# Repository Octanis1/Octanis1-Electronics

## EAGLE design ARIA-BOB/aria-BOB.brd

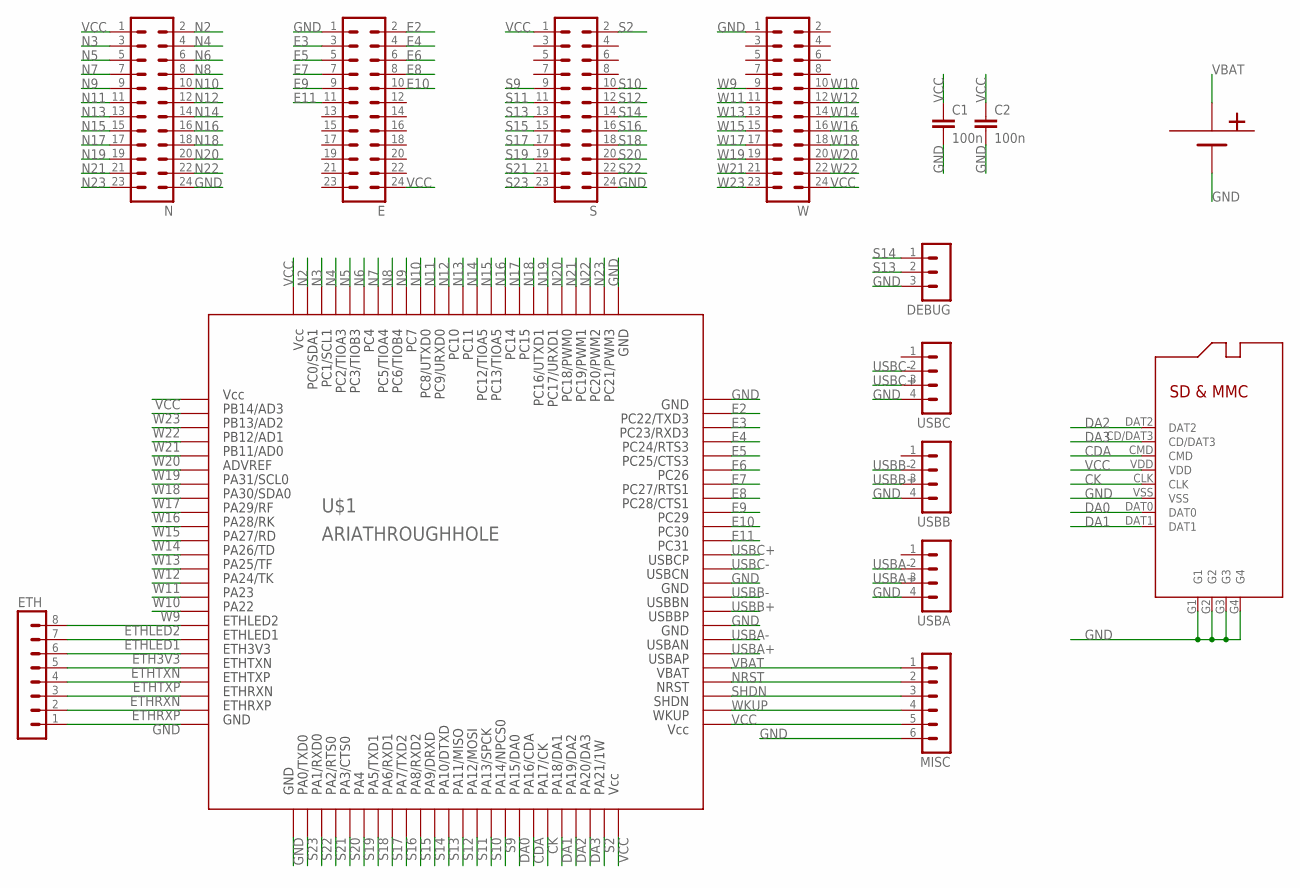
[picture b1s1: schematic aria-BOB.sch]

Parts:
C1, C2: 100n; C0603
DEBUG: MA03-1
E: MA12-2
ETH: MA08-1
MISC: MA06-1
N: MA12-2
S: MA12-2
U$1: ARIATHROUGHHOLE; ARIA-TROUGHHOLE
U$3: BAT; BAT-CR1220
U$4: MICRO-SD; MISCRO-SD
USBA: MA04-1
USBB: MA04-1
USBC: MA04-1
W: MA12-2

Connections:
CDA: U$1.S7, U$4.CMD
CK: U$1.S6, U$4.CLK
DA0: U$1.S8, U$4.DAT0
DA1: U$1.S5, U$4.DAT1
DA2: U$1.S4, U$4.DAT2
DA3: U$1.S3, U$4.CD/DAT3
E2: E.2, U$1.E2
E3: E.3, U$1.E3
E4: E.4, U$1.E4
E5: E.5, U$1.E5
E6: E.6, U$1.E6
E7: E.7, U$1.E7
E8: E.8, U$1.E8
E9: E.9, U$1.E9
E10: E.10, U$1.E10
E11: E.11, U$1.E11
ETH3V3: ETH.6, U$1.W6
ETHLED1: ETH.7, U$1.W7
ETHLED2: ETH.8, U$1.W8
ETHRXN: ETH.3, U$1.W3
ETHRXP: ETH.2, U$1.W2
ETHTXN: ETH.5, U$1.W5
ETHTXP: ETH.4, U$1.W4
GND: C1.2, C2.2, DEBUG.3, E.1, ETH.1, MISC.6, N.24, S.24, U$1.E1, U$1.E14, U$1.E17, U$1.N24, U$1.S24, U$1.W1, U$3.BAT-, U$4.G1, U$4.G2, U$4.G3, U$4.G4, U$4.VSS, USBA.4, USBB.4, USBC.4, W.1
N2: N.2, U$1.N2
N3: N.3, U$1.N3
N4: N.4, U$1.N4
N5: N.5, U$1.N5
N6: N.6, U$1.N6
N7: N.7, U$1.N7
N8: N.8, U$1.N8
N9: N.9, U$1.N9
N10: N.10, U$1.N10
N11: N.11, U$1.N11
N12: N.12, U$1.N12
N13: N.13, U$1.N13
N14: N.14, U$1.N14
N15: N.15, U$1.N15
N16: N.16, U$1.N16
N17: N.17, U$1.N17
N18: N.18, U$1.N18
N19: N.19, U$1.N19
N20: N.20, U$1.N20
N21: N.21, U$1.N21
N22: N.22, U$1.N22
N23: N.23, U$1.N23
NRST: MISC.2, U$1.E21
S2: S.2, U$1.S2
S9: S.9, U$1.S9
S10: S.10, U$1.S10
S11: S.11, U$1.S11
S12: S.12, U$1.S12
S13: DEBUG.2, S.13, U$1.S13
S14: DEBUG.1, S.14, U$1.S14
S15: S.15, U$1.S15
S16: S.16, U$1.S16
S17: S.17, U$1.S17
S18: S.18, U$1.S18
S19: S.19, U$1.S19
S20: S.20, U$1.S20
S21: S.21, U$1.S21
S22: S.22, U$1.S22
S23: S.23, U$1.S23
SHDN: MISC.3, U$1.E22
USBA+: U$1.E19, USBA.3
USBA-: U$1.E18, USBA.2
USBB+: U$1.E16, USBB.3
USBB-: U$1.E15, USBB.2
USBC+: U$1.E12, USBC.3
USBC-: U$1.E13, USBC.2
VBAT: MISC.1, U$1.E20, U$3.BAT1+ (BAT+), U$3.BAT+
VCC: C1.1, C2.1, E.24, MISC.5, N.1, S.1, U$1.E24, U$1.N1, U$1.S1, U$1.W24, U$4.VDD, W.24
W9: U$1.W9, W.9
W10: U$1.W10, W.10
W11: U$1.W11, W.11
W12: U$1.W12, W.12
W13: U$1.W13, W.13
W14: U$1.W14, W.14
W15: U$1.W15, W.15
W16: U$1.W16, W.16
W17: U$1.W17, W.17
W18: U$1.W18, W.18
W19: U$1.W19, W.19
W20: U$1.W20, W.20
W21: U$1.W21, W.21
W22: U$1.W22, W.22
W23: U$1.W23, W.23
WKUP: MISC.4, U$1.E23

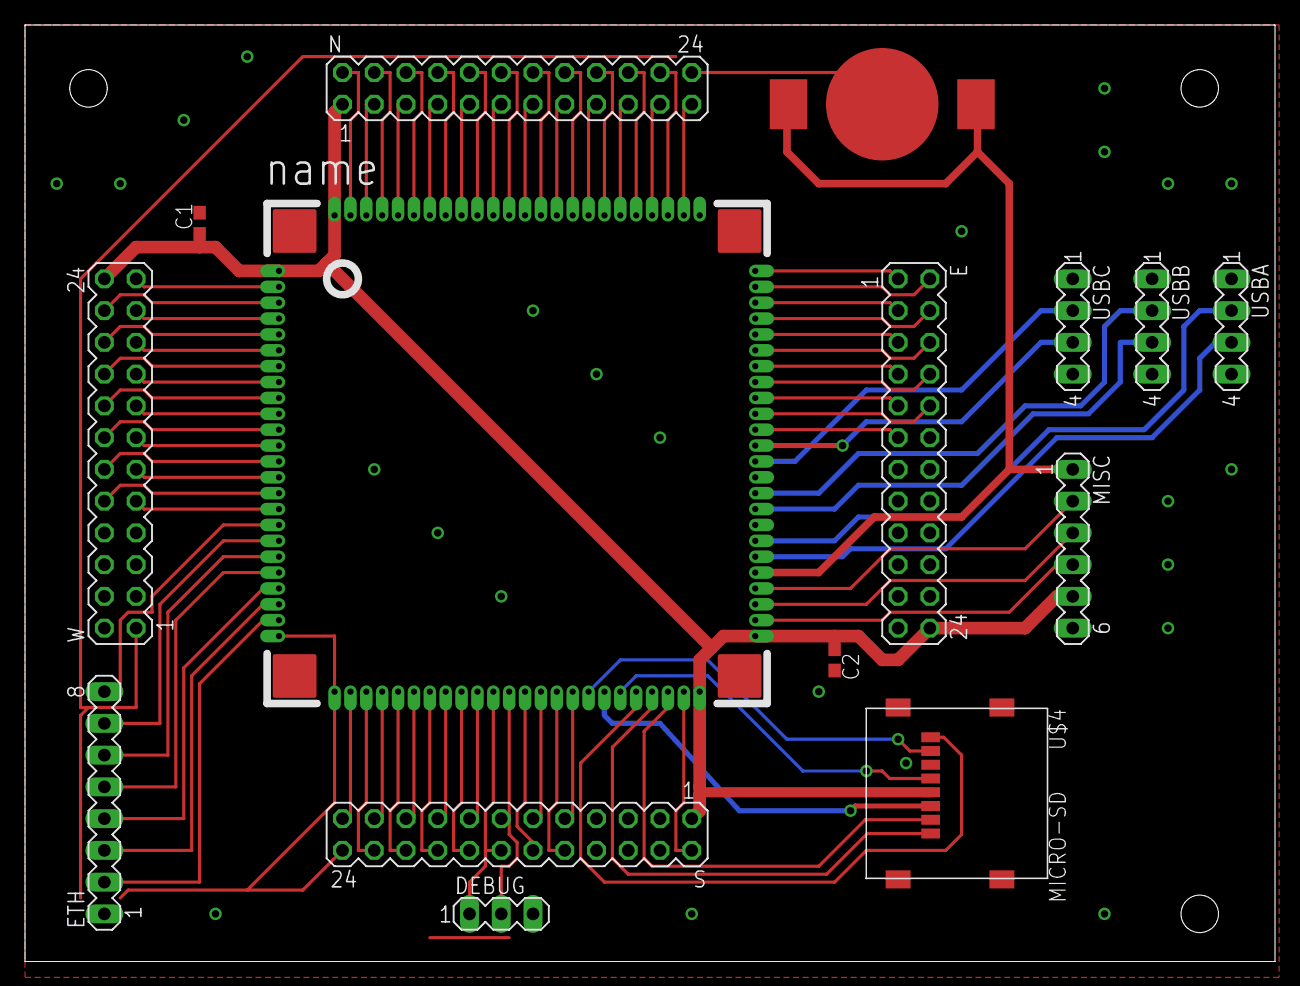
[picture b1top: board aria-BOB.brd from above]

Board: 2 copper layers, 100.0 x 74.9 mm, 15 parts (0 on the bottom side), 88 nets.

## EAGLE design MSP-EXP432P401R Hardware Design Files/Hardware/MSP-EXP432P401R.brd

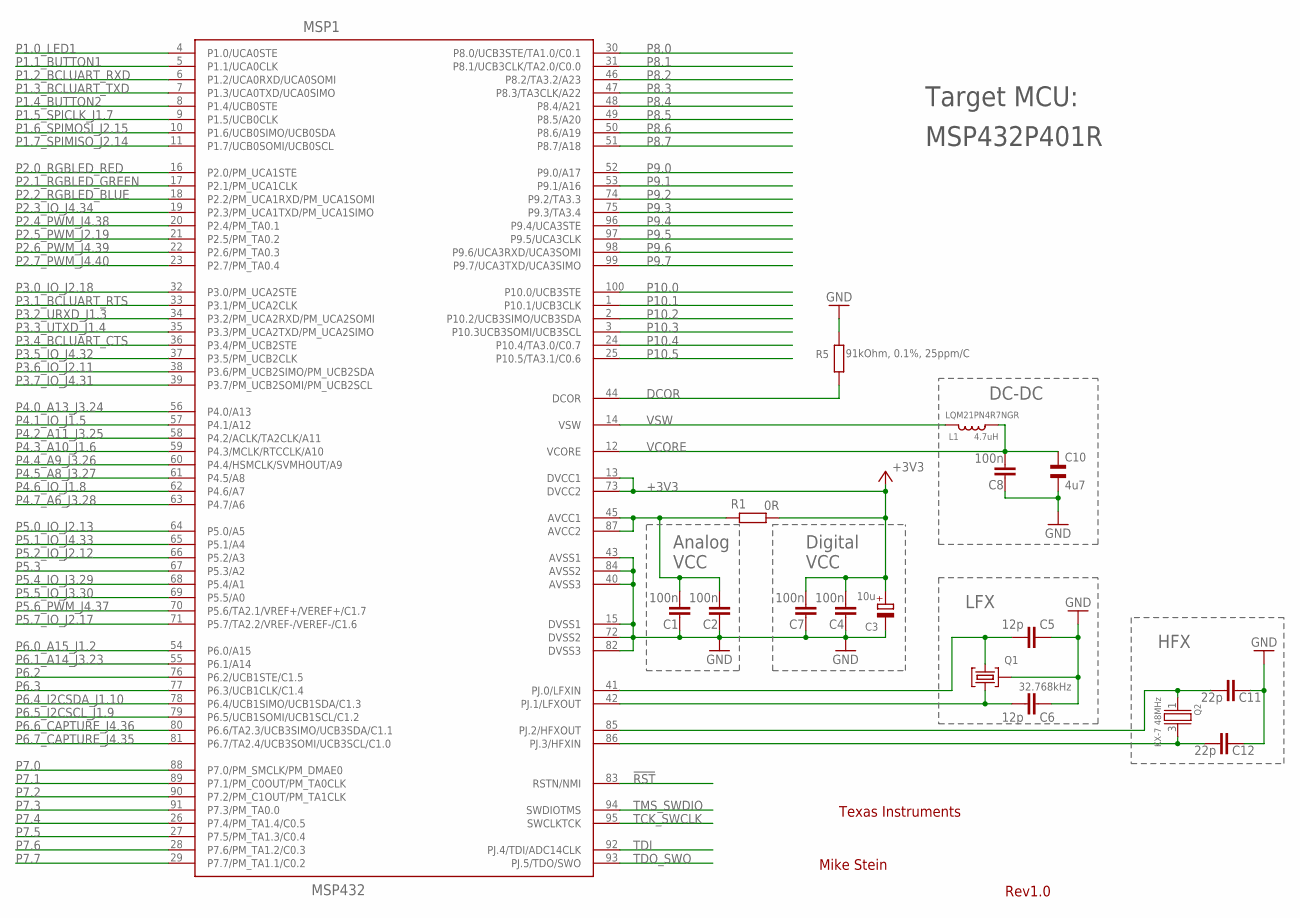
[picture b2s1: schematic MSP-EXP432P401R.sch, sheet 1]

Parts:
C1, C2, C4, C7, C8: 100n; 0402
C3: 10u; A/3216-18R
C5, C6: 12p; 0402
C10: 4u7; CSMD0805
C11, C12: 22p; 0402
L1: 4.7uH; 0806
MSP1: MSP432; PZ100
Q1: 32.768kHz; MS3V-T1R
Q2: KX-7 48MHz; KX-7
R1: 0R; 0402
R5: 91kOhm, 0.1%, 25ppm/C; 0805

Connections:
!RST: MSP1.83 (RSTN/NMI); also elsewhere on the board
+3V3: C3.+, C4.1, C7.1, MSP1.13 (DVCC1), MSP1.73 (DVCC2), R1.1; also elsewhere on the board
DCOR: MSP1.44 (DCOR), R5.1
GND: C1.2, C2.2, C3.-, C4.2, C5.2, C6.2, C7.2, C8.2, C10.2, C11.2, C12.2, MSP1.15 (DVSS1), MSP1.40 (AVSS3), MSP1.43 (AVSS1), MSP1.72 (DVSS2), MSP1.82 (DVSS3), MSP1.84 (AVSS2), Q1.P3 (GND), R5.2; also elsewhere on the board
unnamed: C1.1, C2.1, MSP1.45 (AVCC1), MSP1.87 (AVCC2), R1.2
unnamed: C6.1, MSP1.42 (PJ.1/LFXOUT), Q1.P1 (1)
unnamed: C5.1, MSP1.41 (PJ.0/LFXIN), Q1.P2 (2)
P1.0_LED1: MSP1.4 (P1.0/UCA0STE); also elsewhere on the board
P1.1_BUTTON1: MSP1.5 (P1.1/UCA0CLK); also elsewhere on the board
P1.2_BCLUART_RXD: MSP1.6 (P1.2/UCA0RXD/UCA0SOMI); also elsewhere on the board
P1.3_BCLUART_TXD: MSP1.7 (P1.3/UCA0TXD/UCA0SIMO); also elsewhere on the board
P1.4_BUTTON2: MSP1.8 (P1.4/UCB0STE); also elsewhere on the board
P1.5_SPICLK_J1.7: MSP1.9 (P1.5/UCB0CLK); also elsewhere on the board
P1.6_SPIMOSI_J2.15: MSP1.10 (P1.6/UCB0SIMO/UCB0SDA); also elsewhere on the board
P1.7_SPIMISO_J2.14: MSP1.11 (P1.7/UCB0SOMI/UCB0SCL); also elsewhere on the board
P2.0_RGBLED_RED: MSP1.16 (P2.0/PM_UCA1STE); also elsewhere on the board
P2.1_RGBLED_GREEN: MSP1.17 (P2.1/PM_UCA1CLK); also elsewhere on the board
P2.2_RGBLED_BLUE: MSP1.18 (P2.2/PM_UCA1RXD/PM_UCA1SOMI); also elsewhere on the board
P2.3_IO_J4.34: MSP1.19 (P2.3/PM_UCA1TXD/PM_UCA1SIMO); also elsewhere on the board
P2.4_PWM_J4.38: MSP1.20 (P2.4/PM_TA0.1); also elsewhere on the board
P2.5_PWM_J2.19: MSP1.21 (P2.5/PM_TA0.2); also elsewhere on the board
P2.6_PWM_J4.39: MSP1.22 (P2.6/PM_TA0.3); also elsewhere on the board
P2.7_PWM_J4.40: MSP1.23 (P2.7/PM_TA0.4); also elsewhere on the board
P3.0_IO_J2.18: MSP1.32 (P3.0/PM_UCA2STE); also elsewhere on the board
P3.1_BCLUART_RTS: MSP1.33 (P3.1/PM_UCA2CLK); also elsewhere on the board
P3.2_URXD_J1.3: MSP1.34 (P3.2/PM_UCA2RXD/PM_UCA2SOMI); also elsewhere on the board
P3.3_UTXD_J1.4: MSP1.35 (P3.3/PM_UCA2TXD/PM_UCA2SIMO); also elsewhere on the board
P3.4_BCLUART_CTS: MSP1.36 (P3.4/PM_UCB2STE); also elsewhere on the board
P3.5_IO_J4.32: MSP1.37 (P3.5/PM_UCB2CLK); also elsewhere on the board
P3.6_IO_J2.11: MSP1.38 (P3.6/PM_UCB2SIMO/PM_UCB2SDA); also elsewhere on the board
P3.7_IO_J4.31: MSP1.39 (P3.7/PM_UCB2SOMI/PM_UCB2SCL); also elsewhere on the board
P4.0_A13_J3.24: MSP1.56 (P4.0/A13); also elsewhere on the board
P4.1_IO_J1.5: MSP1.57 (P4.1/A12); also elsewhere on the board
P4.2_A11_J3.25: MSP1.58 (P4.2/ACLK/TA2CLK/A11); also elsewhere on the board
P4.3_A10_J1.6: MSP1.59 (P4.3/MCLK/RTCCLK/A10); also elsewhere on the board
P4.4_A9_J3.26: MSP1.60 (P4.4/HSMCLK/SVMHOUT/A9); also elsewhere on the board
P4.5_A8_J3.27: MSP1.61 (P4.5/A8); also elsewhere on the board
P4.6_IO_J1.8: MSP1.62 (P4.6/A7); also elsewhere on the board
P4.7_A6_J3.28: MSP1.63 (P4.7/A6); also elsewhere on the board
P5.0_IO_J2.13: MSP1.64 (P5.0/A5); also elsewhere on the board
P5.1_IO_J4.33: MSP1.65 (P5.1/A4); also elsewhere on the board
P5.2/XT2IN: C12.1, MSP1.86 (PJ.3/HFXIN), Q2.3 (2)
P5.2_IO_J2.12: MSP1.66 (P5.2/A3); also elsewhere on the board
P5.3: MSP1.67 (P5.3/A2); also elsewhere on the board
P5.3/XT2OUT: C11.1, MSP1.85 (PJ.2/HFXOUT), Q2.1
P5.4_IO_J3.29: MSP1.68 (P5.4/A1); also elsewhere on the board
P5.5_IO_J3.30: MSP1.69 (P5.5/A0); also elsewhere on the board
P5.6_PWM_J4.37: MSP1.70 (P5.6/TA2.1/VREF+/VEREF+/C1.7); also elsewhere on the board
P5.7_IO_J2.17: MSP1.71 (P5.7/TA2.2/VREF-/VEREF-/C1.6); also elsewhere on the board
P6.0_A15_J1.2: MSP1.54 (P6.0/A15); also elsewhere on the board
P6.1_A14_J3.23: MSP1.55 (P6.1/A14); also elsewhere on the board
P6.2: MSP1.76 (P6.2/UCB1STE/C1.5); also elsewhere on the board
P6.3: MSP1.77 (P6.3/UCB1CLK/C1.4); also elsewhere on the board
P6.4_I2CSDA_J1.10: MSP1.78 (P6.4/UCB1SIMO/UCB1SDA/C1.3); also elsewhere on the board
P6.5_I2CSCL_J1.9: MSP1.79 (P6.5/UCB1SOMI/UCB1SCL/C1.2); also elsewhere on the board
P6.6_CAPTURE_J4.36: MSP1.80 (P6.6/TA2.3/UCB3SIMO/UCB3SDA/C1.1); also elsewhere on the board
P6.7_CAPTURE_J4.35: MSP1.81 (P6.7/TA2.4/UCB3SOMI/UCB3SCL/C1.0); also elsewhere on the board
P7.0: MSP1.88 (P7.0/PM_SMCLK/PM_DMAE0); also elsewhere on the board
P7.1: MSP1.89 (P7.1/PM_C0OUT/PM_TA0CLK); also elsewhere on the board
P7.2: MSP1.90 (P7.2/PM_C1OUT/PM_TA1CLK); also elsewhere on the board
P7.3: MSP1.91 (P7.3/PM_TA0.0); also elsewhere on the board
P7.4: MSP1.26 (P7.4/PM_TA1.4/C0.5); also elsewhere on the board
P7.5: MSP1.27 (P7.5/PM_TA1.3/C0.4); also elsewhere on the board
P7.6: MSP1.28 (P7.6/PM_TA1.2/C0.3); also elsewhere on the board
P7.7: MSP1.29 (P7.7/PM_TA1.1/C0.2); also elsewhere on the board
P8.0: MSP1.30 (P8.0/UCB3STE/TA1.0/C0.1); also elsewhere on the board
P8.1: MSP1.31 (P8.1/UCB3CLK/TA2.0/C0.0)
P8.2: MSP1.46 (P8.2/TA3.2/A23); also elsewhere on the board
P8.3: MSP1.47 (P8.3/TA3CLK/A22); also elsewhere on the board
P8.4: MSP1.48 (P8.4/A21); also elsewhere on the board
P8.5: MSP1.49 (P8.5/A20); also elsewhere on the board
P8.6: MSP1.50 (P8.6/A19); also elsewhere on the board
P8.7: MSP1.51 (P8.7/A18); also elsewhere on the board
P9.0: MSP1.52 (P9.0/A17); also elsewhere on the board
P9.1: MSP1.53 (P9.1/A16); also elsewhere on the board
P9.2: MSP1.74 (P9.2/TA3.3); also elsewhere on the board
P9.3: MSP1.75 (P9.3/TA3.4); also elsewhere on the board
P9.4: MSP1.96 (P9.4/UCA3STE); also elsewhere on the board
P9.5: MSP1.97 (P9.5/UCA3CLK); also elsewhere on the board
P9.6: MSP1.98 (P9.6/UCA3RXD/UCA3SOMI); also elsewhere on the board
P9.7: MSP1.99 (P9.7/UCA3TXD/UCA3SIMO); also elsewhere on the board
P10.0: MSP1.100 (P10.0/UCB3STE); also elsewhere on the board
P10.1: MSP1.1 (P10.1/UCB3CLK); also elsewhere on the board
P10.2: MSP1.2 (P10.2/UCB3SIMO/UCB3SDA); also elsewhere on the board
P10.3: MSP1.3 (P10.3UCB3SOMI/UCB3SCL); also elsewhere on the board
P10.4: MSP1.24 (P10.4/TA3.0/C0.7); also elsewhere on the board
P10.5: MSP1.25 (P10.5/TA3.1/C0.6); also elsewhere on the board
TCK_SWCLK: MSP1.95 (SWCLKTCK); also elsewhere on the board
TDI: MSP1.92 (PJ.4/TDI/ADC14CLK); also elsewhere on the board
TDO_SWO: MSP1.93 (PJ.5/TDO/SWO); also elsewhere on the board
TMS_SWDIO: MSP1.94 (SWDIOTMS); also elsewhere on the board
VCORE: C8.1, C10.1, L1.1, MSP1.12 (VCORE)
VSW: L1.2, MSP1.14 (VSW)

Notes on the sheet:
Target MCU:
Texas Instruments
Mike Stein
Rev1.0
LQM21PN4R7NGR
HFX
LFX
Analog
VCC
Digital
DC-DC
MSP432P401R

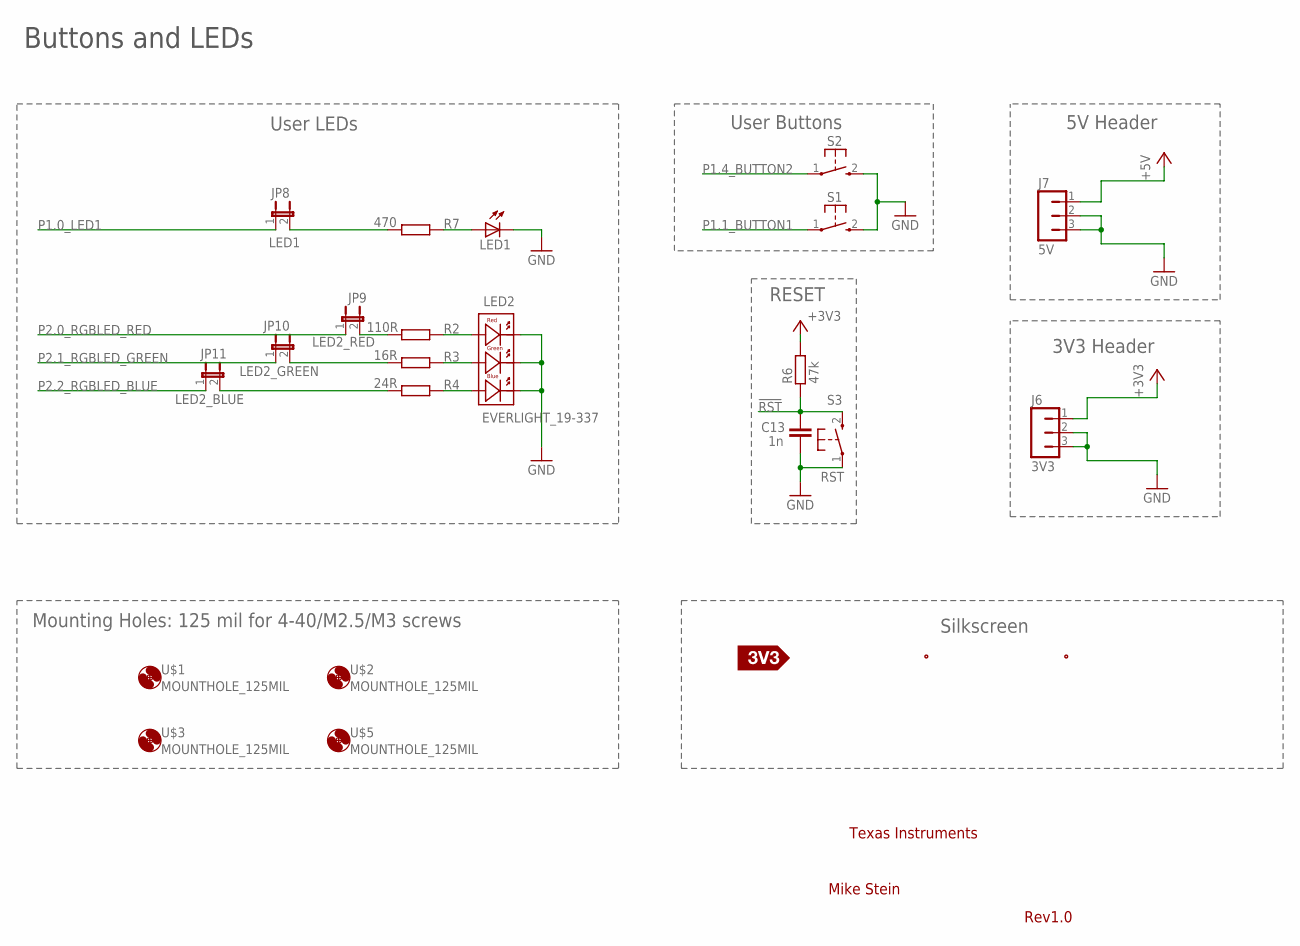
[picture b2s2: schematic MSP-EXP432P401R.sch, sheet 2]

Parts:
C13: 1n; 0402
J6: 3V3; JP3
J7: 5V; JP3
JP8: LED1; JP1M
JP9: LED2_RED; JP1M
JP10: LED2_GREEN; JP1M
JP11: LED2_BLUE; JP1M
LED1: LEDCHIPLED_0603; CHIPLED_0603
LED2: EVERLIGHT_19-337; RGB_LED
R2: 110R; 0402
R3: 16R; 0402
R4: 24R; 0402
R6: 47k; 0402
R7: 470; 0402
S1, S2: PB; PBTH
S3: RST; PBTH
U$1, U$2, U$3, U$5: MOUNTHOLE_125MIL
U$6: SILK_HEADER_LABEL
U$7: SILK_3V3_TAG
U$8: SILK_P401R_REAR

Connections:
!RST: C13.1, R6.1, S3.2 (S); also elsewhere on the board
+3V3: J6.1, R6.2; also elsewhere on the board
+5V: J7.1; also elsewhere on the board
GND: C13.2, J6.2, J6.3, J7.2, J7.3, LED1.C, LED2.1 (BC), LED2.2 (RC), LED2.3 (GC), S1.2 (S), S2.2 (S), S3.1; also elsewhere on the board
unnamed: JP9.2, R2.1
unnamed: LED2.5 (RA), R2.2
unnamed: LED2.6 (GA), R3.2
unnamed: LED2.4 (BA), R4.2
unnamed: LED1.A, R7.2
unnamed: JP10.2, R3.1
unnamed: JP11.2, R4.1
unnamed: JP8.2, R7.1
P1.0_LED1: JP8.1; also elsewhere on the board
P1.1_BUTTON1: S1.1; also elsewhere on the board
P1.4_BUTTON2: S2.1; also elsewhere on the board
P2.0_RGBLED_RED: JP9.1; also elsewhere on the board
P2.1_RGBLED_GREEN: JP10.1; also elsewhere on the board
P2.2_RGBLED_BLUE: JP11.1; also elsewhere on the board

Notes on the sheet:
User LEDs
User Buttons
RESET
Buttons and LEDs
5V Header
3V3 Header
Mounting Holes: 125 mil for 4-40/M2.5/M3 screws
Silkscreen
Texas Instruments
Mike Stein
Rev1.0

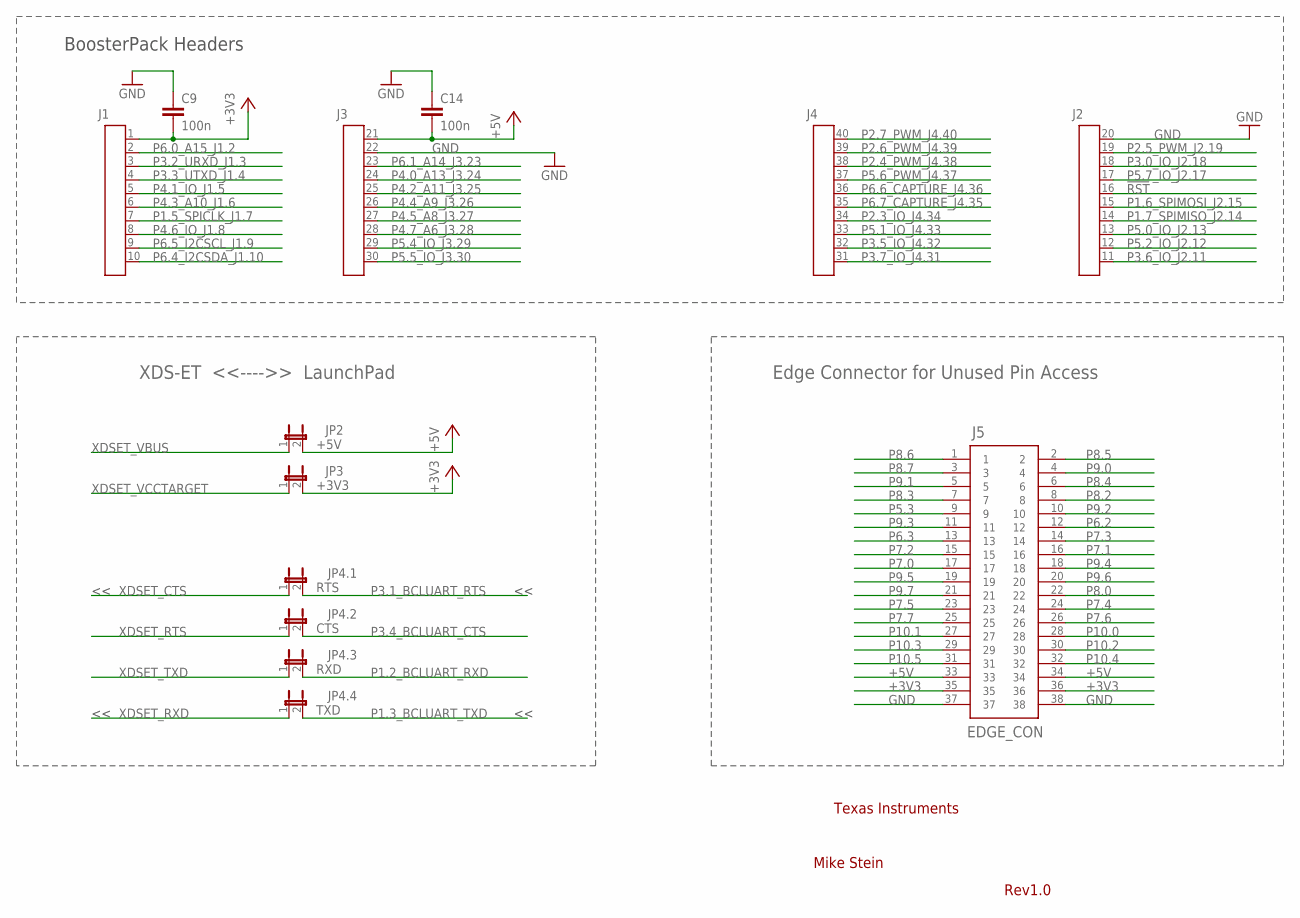
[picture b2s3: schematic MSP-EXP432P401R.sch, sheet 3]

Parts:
C9, C14: 100n; 0402
J1: HEADER1X10; 1X10
J2: HEADER1X10-J2; 1X10-J2
J3: HEADER1X10-J3; 1X10-J3
J4: HEADER1X10-J4; 1X10-J4
J5: EDGE_CON; BOTTOM_CONNECTOR
JP2: +5V; JP1M
JP3: +3V3; JP1M
JP4.1: RTS; JP1M
JP4.2: CTS; JP1M
JP4.3: RXD; JP1M
JP4.4: TXD; JP1M

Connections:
!RST: J2.16 (5); also elsewhere on the board
+3V3: C9.2, J1.1, J5.35, J5.36, JP3.2; also elsewhere on the board
+5V: C14.2, J3.21 (1), J5.33, J5.34, JP2.2; also elsewhere on the board
GND: C9.1, C14.1, J2.20 (1), J3.22 (2), J5.37, J5.38; also elsewhere on the board
P1.2_BCLUART_RXD: JP4.3.2; also elsewhere on the board
P1.3_BCLUART_TXD: JP4.4.2; also elsewhere on the board
P1.5_SPICLK_J1.7: J1.7; also elsewhere on the board
P1.6_SPIMOSI_J2.15: J2.15 (6); also elsewhere on the board
P1.7_SPIMISO_J2.14: J2.14 (7); also elsewhere on the board
P2.3_IO_J4.34: J4.34 (7); also elsewhere on the board
P2.4_PWM_J4.38: J4.38 (3); also elsewhere on the board
P2.5_PWM_J2.19: J2.19 (2); also elsewhere on the board
P2.6_PWM_J4.39: J4.39 (2); also elsewhere on the board
P2.7_PWM_J4.40: J4.40 (1); also elsewhere on the board
P3.0_IO_J2.18: J2.18 (3); also elsewhere on the board
P3.1_BCLUART_RTS: JP4.1.2; also elsewhere on the board
P3.2_URXD_J1.3: J1.3; also elsewhere on the board
P3.3_UTXD_J1.4: J1.4; also elsewhere on the board
P3.4_BCLUART_CTS: JP4.2.2; also elsewhere on the board
P3.5_IO_J4.32: J4.32 (9); also elsewhere on the board
P3.6_IO_J2.11: J2.11 (10); also elsewhere on the board
P3.7_IO_J4.31: J4.31 (10); also elsewhere on the board
P4.0_A13_J3.24: J3.24 (4); also elsewhere on the board
P4.1_IO_J1.5: J1.5; also elsewhere on the board
P4.2_A11_J3.25: J3.25 (5); also elsewhere on the board
P4.3_A10_J1.6: J1.6; also elsewhere on the board
P4.4_A9_J3.26: J3.26 (6); also elsewhere on the board
P4.5_A8_J3.27: J3.27 (7); also elsewhere on the board
P4.6_IO_J1.8: J1.8; also elsewhere on the board
P4.7_A6_J3.28: J3.28 (8); also elsewhere on the board
P5.0_IO_J2.13: J2.13 (8); also elsewhere on the board
P5.1_IO_J4.33: J4.33 (8); also elsewhere on the board
P5.2_IO_J2.12: J2.12 (9); also elsewhere on the board
P5.3: J5.9; also elsewhere on the board
P5.4_IO_J3.29: J3.29 (9); also elsewhere on the board
P5.5_IO_J3.30: J3.30 (10); also elsewhere on the board
P5.6_PWM_J4.37: J4.37 (4); also elsewhere on the board
P5.7_IO_J2.17: J2.17 (4); also elsewhere on the board
P6.0_A15_J1.2: J1.2; also elsewhere on the board
P6.1_A14_J3.23: J3.23 (3); also elsewhere on the board
P6.2: J5.12; also elsewhere on the board
P6.3: J5.13; also elsewhere on the board
P6.4_I2CSDA_J1.10: J1.10; also elsewhere on the board
P6.5_I2CSCL_J1.9: J1.9; also elsewhere on the board
P6.6_CAPTURE_J4.36: J4.36 (5); also elsewhere on the board
P6.7_CAPTURE_J4.35: J4.35 (6); also elsewhere on the board
P7.0: J5.17; also elsewhere on the board
P7.1: J5.16; also elsewhere on the board
P7.2: J5.15; also elsewhere on the board
P7.3: J5.14; also elsewhere on the board
P7.4: J5.24; also elsewhere on the board
P7.5: J5.23; also elsewhere on the board
P7.6: J5.26; also elsewhere on the board
P7.7: J5.25; also elsewhere on the board
P8.0: J5.22; also elsewhere on the board
P8.2: J5.8; also elsewhere on the board
P8.3: J5.7; also elsewhere on the board
P8.4: J5.6; also elsewhere on the board
P8.5: J5.2; also elsewhere on the board
P8.6: J5.1; also elsewhere on the board
P8.7: J5.3; also elsewhere on the board
P9.0: J5.4; also elsewhere on the board
P9.1: J5.5; also elsewhere on the board
P9.2: J5.10; also elsewhere on the board
P9.3: J5.11; also elsewhere on the board
P9.4: J5.18; also elsewhere on the board
P9.5: J5.19; also elsewhere on the board
P9.6: J5.20; also elsewhere on the board
P9.7: J5.21; also elsewhere on the board
P10.0: J5.28; also elsewhere on the board
P10.1: J5.27; also elsewhere on the board
P10.2: J5.30; also elsewhere on the board
P10.3: J5.29; also elsewhere on the board
P10.4: J5.32; also elsewhere on the board
P10.5: J5.31; also elsewhere on the board
XDSET_CTS: JP4.1.1; also elsewhere on the board
XDSET_RTS: JP4.2.1; also elsewhere on the board
XDSET_RXD: JP4.4.1; also elsewhere on the board
XDSET_TXD: JP4.3.1; also elsewhere on the board
XDSET_VBUS: JP2.1; also elsewhere on the board
XDSET_VCCTARGET: JP3.1; also elsewhere on the board

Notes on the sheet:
BoosterPack Headers
XDS-ET <<---->> LaunchPad
Edge Connector for Unused Pin Access
Texas Instruments
Mike Stein
Rev1.0

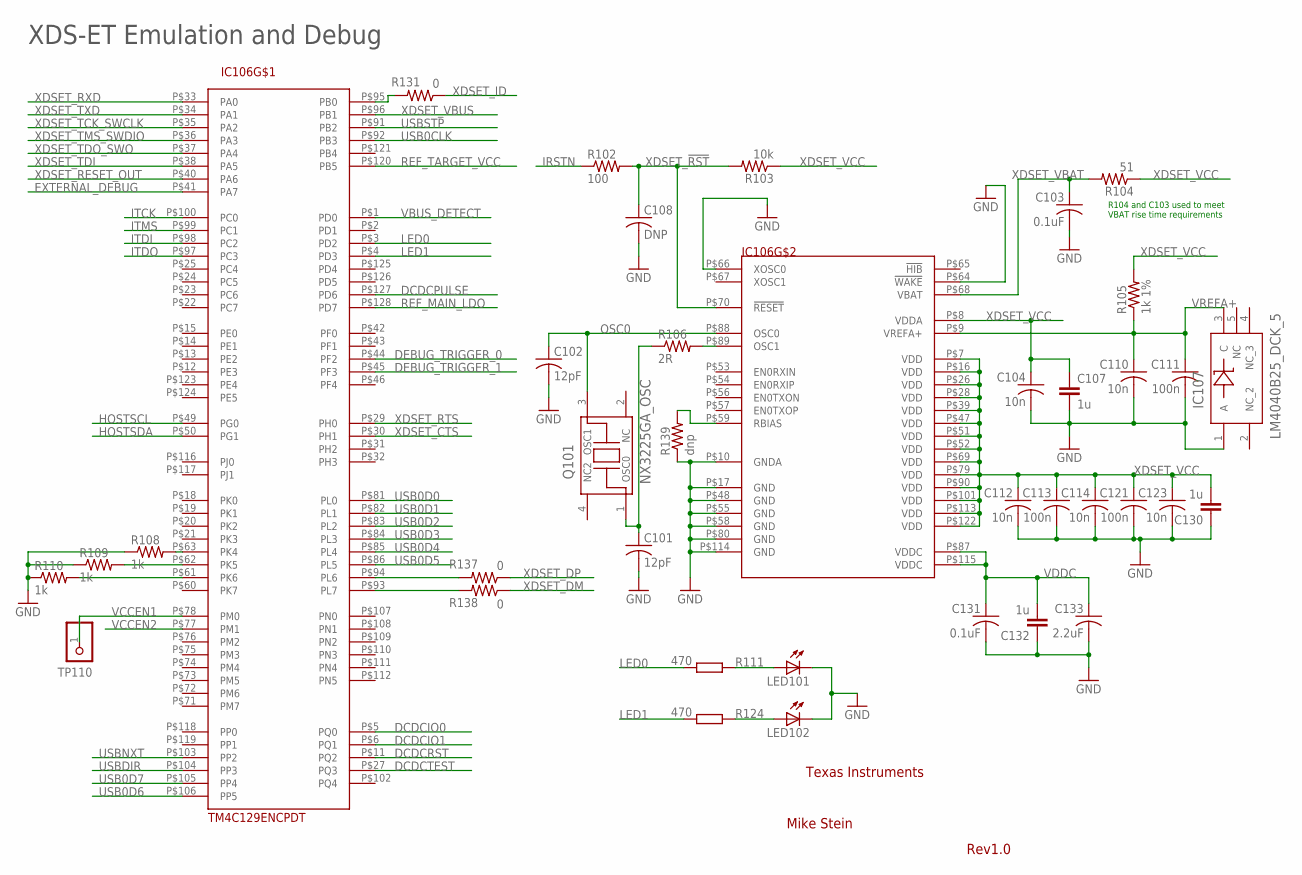
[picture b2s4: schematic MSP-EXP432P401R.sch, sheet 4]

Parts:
C101, C102: 12pF; C0402
C103, C131: 0.1uF; C0402
C104, C110, C112, C114, C123: 10n; C0402
C107, C130, C132: 1u; C0603
C108: DNP; C0402
C111, C113, C121: 100n; C0402
C133: 2.2uF; C0603K; DIGIKEY_PARTNUM 311-1451-2-ND
IC106: TM4C129ENCPDT; TQFP-128
IC107: LM4040B25_DCK_5; DCK5
LED101, LED102: LEDCHIPLED_0603; CHIPLED_0603
Q101: NX3225GA_OSC; NX3225GA
R102: 100; R0402
R103: 10k; R0402
R104: 51; R0402
R105: 1k 1%; R0402
R106: 2R; R0402
R108, R109, R110: 1k; R0402
R111, R124: 470; 0402
R131, R137, R138: 0; R0402
R139: dnp; R0402
TP110: TEST_PIN2; 1X01

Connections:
DCDCIO0: IC106.P$5 (PQ0); also elsewhere on the board
DCDCIO1: IC106.P$6 (PQ1); also elsewhere on the board
DCDCPULSE: IC106.P$127 (PD6); also elsewhere on the board
DCDCRST: IC106.P$11 (PQ2); also elsewhere on the board
DCDCTEST: IC106.P$27 (PQ3); also elsewhere on the board
DEBUG_TRIGGER_0: IC106.P$44 (PF2)
DEBUG_TRIGGER_1: IC106.P$45 (PF3)
EXTERNAL_DEBUG: IC106.P$41 (PA7)
GND: C101.2, C102.2, C103.2, C104.2, C107.2, C108.2, C110.2, C111.2, C112.2, C113.2, C114.2, C121.2, C123.2, C130.1, C131.2, C132.1, C133.2, IC106.P$10 (GNDA), IC106.P$17 (GND), IC106.P$48 (GND), IC106.P$55 (GND), IC106.P$58 (GND), IC106.P$64 (!WAKE), IC106.P$66 (XOSC0), IC106.P$80 (GND), IC106.P$114 (GND), IC107.1 (A), LED101.C, LED102.C, R108.1, R109.1, R110.1, R139.1; also elsewhere on the board
HOSTSCL: IC106.P$49 (PG0); also elsewhere on the board
HOSTSDA: IC106.P$50 (PG1); also elsewhere on the board
IRSTN: R102.1; also elsewhere on the board
ITCK: IC106.P$100 (PC0); also elsewhere on the board
ITDI: IC106.P$98 (PC2); also elsewhere on the board
ITDO: IC106.P$97 (PC3); also elsewhere on the board
ITMS: IC106.P$99 (PC1); also elsewhere on the board
LED0: IC106.P$3 (PD2), R111.1
LED1: IC106.P$4 (PD3), R124.1
unnamed: IC106.P$63 (PK4), R108.2
unnamed: LED102.A, R124.2
unnamed: LED101.A, R111.2
unnamed: IC106.P$93 (PL7), R138.2
unnamed: IC106.P$61 (PK6), R110.2
unnamed: IC106.P$95 (PB0), R131.2
unnamed: IC106.P$62 (PK5), R109.2
unnamed: IC106.P$59 (RBIAS), R139.2
OSC0: C102.1, IC106.P$88 (OSC0), Q101.3 (OSC1)
OSC1: IC106.P$89 (OSC1), R106.2
OSC1_R: C101.1, Q101.1 (OSC0), R106.1
REF_MAIN_LDO: IC106.P$128 (PD7); also elsewhere on the board
REF_TARGET_VCC: IC106.P$120 (PB5); also elsewhere on the board
USB0CLK: IC106.P$92 (PB3); also elsewhere on the board
USB0D0: IC106.P$81 (PL0); also elsewhere on the board
USB0D1: IC106.P$82 (PL1); also elsewhere on the board
USB0D2: IC106.P$83 (PL2); also elsewhere on the board
USB0D3: IC106.P$84 (PL3); also elsewhere on the board
USB0D4: IC106.P$85 (PL4); also elsewhere on the board
USB0D5: IC106.P$86 (PL5); also elsewhere on the board
USB0D6: IC106.P$106 (PP5); also elsewhere on the board
USB0D7: IC106.P$105 (PP4); also elsewhere on the board
USBDIR: IC106.P$104 (PP3); also elsewhere on the board
USBNXT: IC106.P$103 (PP2); also elsewhere on the board
USBSTP: IC106.P$91 (PB2); also elsewhere on the board
VBUS_DETECT: IC106.P$1 (PD0); also elsewhere on the board
VCCEN1: IC106.P$78 (PM0), TP110.1; also elsewhere on the board
VCCEN2: IC106.P$77 (PM1)
VDDC: C131.1, C132.2, C133.1, IC106.P$87 (VDDC), IC106.P$115 (VDDC)
VREFA+: C110.1, C111.1, IC106.P$9 (VREFA+), IC107.3 (C), R105.1
XDSET_!RST: C108.1, IC106.P$70 (!RESET), R102.2, R103.2
XDSET_CTS: IC106.P$30 (PH1); also elsewhere on the board
XDSET_DM: R138.1; also elsewhere on the board
XDSET_DP: R137.1; also elsewhere on the board
XDSET_DPR: IC106.P$94 (PL6), R137.2
XDSET_ID: R131.1; also elsewhere on the board
XDSET_RESET_OUT: IC106.P$40 (PA6); also elsewhere on the board
XDSET_RTS: IC106.P$29 (PH0); also elsewhere on the board
XDSET_RXD: IC106.P$33 (PA0); also elsewhere on the board
XDSET_TCK_SWCLK: IC106.P$35 (PA2); also elsewhere on the board
XDSET_TDI: IC106.P$38 (PA5); also elsewhere on the board
XDSET_TDO_SWO: IC106.P$37 (PA4); also elsewhere on the board
XDSET_TMS_SWDIO: IC106.P$36 (PA3); also elsewhere on the board
XDSET_TXD: IC106.P$34 (PA1); also elsewhere on the board
XDSET_VBAT: C103.1, IC106.P$68 (VBAT), R104.2
XDSET_VBUS: IC106.P$96 (PB1); also elsewhere on the board
XDSET_VCC: C104.1, C107.1, C112.1, C113.1, C114.1, C121.1, C123.1, C130.2, IC106.P$7 (VDD), IC106.P$8 (VDDA), IC106.P$16 (VDD), IC106.P$26 (VDD), IC106.P$28 (VDD), IC106.P$39 (VDD), IC106.P$47 (VDD), IC106.P$51 (VDD), IC106.P$52 (VDD), IC106.P$69 (VDD), IC106.P$79 (VDD), IC106.P$90 (VDD), IC106.P$101 (VDD), IC106.P$113 (VDD), IC106.P$122 (VDD), R103.1, R104.1, R105.2; also elsewhere on the board

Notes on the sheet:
R104 and C103 used to meet VBAT rise time requirements
XDS-ET Emulation and Debug
Texas Instruments
Mike Stein
Rev1.0

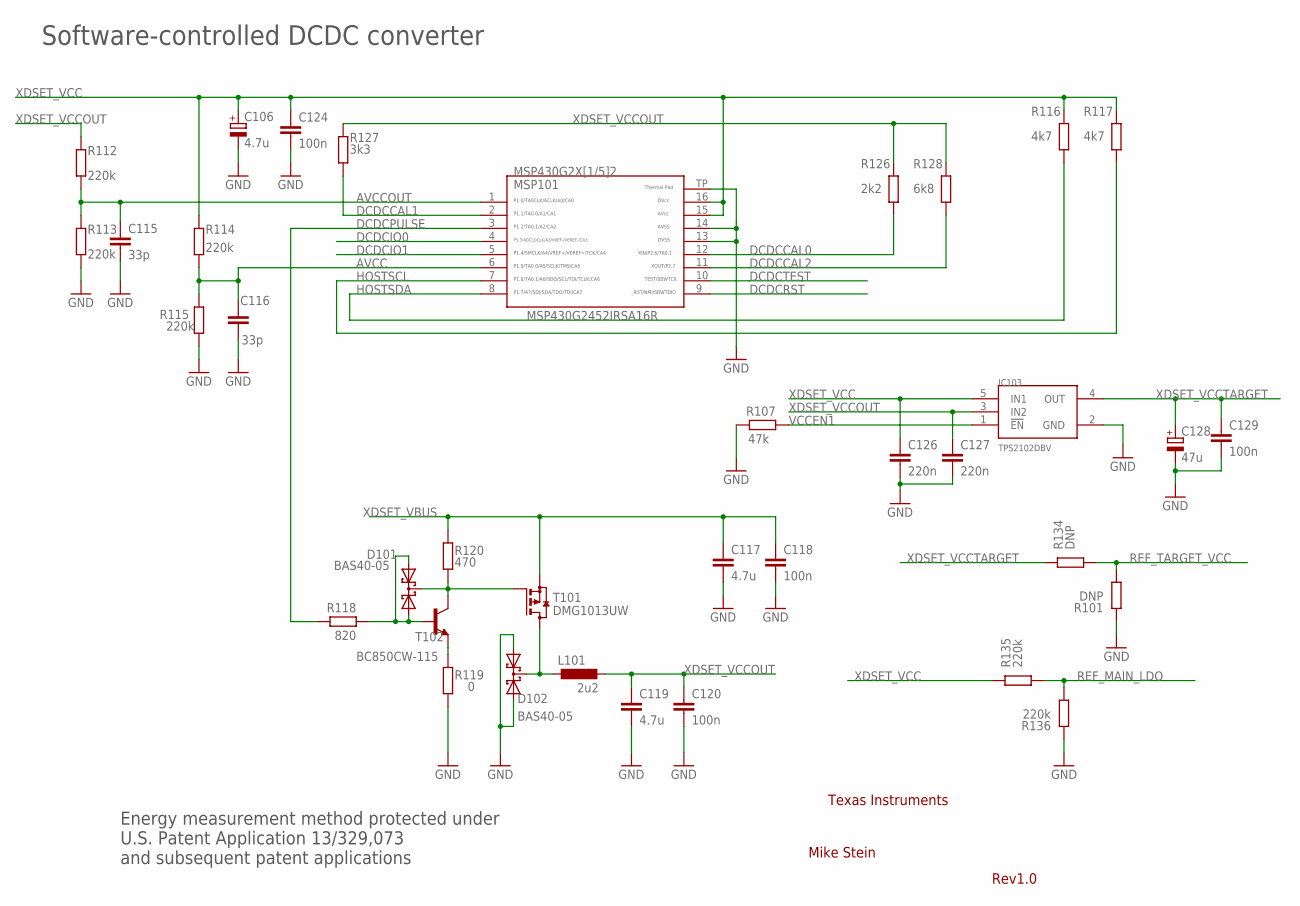
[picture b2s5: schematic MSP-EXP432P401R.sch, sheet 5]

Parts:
C106: 4.7u; A/3216-18R
C115, C116: 33p; 0402
C117, C119: 4.7u; C0603
C118, C120, C124, C129: 100n; 0402
C126, C127: 220n; 0402
C128: 47u; A/3216-18R
D101, D102: BAS40-05; SOT23
IC103: TPS2102DBV; SOT23-5
L101: 2u2; L3216C
MSP101: MSP430G2452IRSA16R; RSA16
R101, R134: DNP; 0402
R107: 47k; 0402
R112, R113, R114, R115, R135, R136: 220k; 0402
R116, R117: 4k7; 0402
R118: 820; 0402
R119: 0; 0402
R120: 470; 0402
R126: 2k2; 0402
R127: 3k3; 0402
R128: 6k8; 0402
T101: DMG1013UW; SOT23
T102: BC850CW-115; SOT23-BEC

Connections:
AVCC: C116.2, MSP101.6, R114.2, R115.1
AVCCOUT: C115.2, MSP101.1, R112.2, R113.1
DCDCCAL0: MSP101.12, R126.2
DCDCCAL1: MSP101.2, R127.2
DCDCCAL2: MSP101.11, R128.2
DCDCIO0: MSP101.4; also elsewhere on the board
DCDCIO1: MSP101.5; also elsewhere on the board
DCDCPULSE: MSP101.3, R118.2; also elsewhere on the board
DCDCRST: MSP101.9; also elsewhere on the board
DCDCTEST: MSP101.10; also elsewhere on the board
GND: C106.-, C115.1, C116.1, C117.2, C118.2, C119.2, C120.2, C124.2, C126.2, C127.2, C128.-, C129.2, D102.1 (A1), D102.2 (A2), IC103.2 (GND), MSP101.13, MSP101.14, MSP101.TP, R101.1, R107.2, R113.2, R115.2, R119.2, R136.1; also elsewhere on the board
HOSTSCL: MSP101.7, R117.2; also elsewhere on the board
HOSTSDA: MSP101.8, R116.2; also elsewhere on the board
unnamed: R119.1, T102.E
unnamed: D101.1 (A1), D101.2 (A2), R118.1, T102.B
unnamed: D102.3 (C), L101.1, T101.3 (D)
unnamed: D101.3 (C), R120.2, T101.1 (G), T102.C
REF_MAIN_LDO: R135.2, R136.2; also elsewhere on the board
REF_TARGET_VCC: R101.2, R134.2; also elsewhere on the board
VCCEN1: IC103.1 (!EN), R107.1; also elsewhere on the board
XDSET_VBUS: C117.1, C118.1, R120.1, T101.2 (S); also elsewhere on the board
XDSET_VCC: C106.+, C124.1, C126.1, IC103.5 (IN1), MSP101.15, MSP101.16, R114.1, R116.1, R117.1, R135.1; also elsewhere on the board
XDSET_VCCOUT: C119.1, C120.1, C127.1, IC103.3 (IN2), L101.2, R112.1, R126.1, R127.1, R128.1
XDSET_VCCTARGET: C128.+, C129.1, IC103.4 (OUT), R134.1; also elsewhere on the board

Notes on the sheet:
Software-controlled DCDC converter
MSP430G2452IRSA16R
Energy measurement method protected under U.S. Patent Application 13/329,073 and subsequent patent applications
Texas Instruments
Mike Stein
Rev1.0

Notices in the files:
MSP-EXP432P401R Hardware Design Files/Hardware/MSP-EXP432P401R.brd:
(C)2003 A. DANNENBERG
parts and their libraries:
TI-LaunchPad-Eagle: As far as I know the LaunchPad rocket is released by TI under the Creative Commons license.
SparkFun-Capacitors: Licensing: CC v3.0 Share-Alike You are welcome to use this library for commercial purposes.
